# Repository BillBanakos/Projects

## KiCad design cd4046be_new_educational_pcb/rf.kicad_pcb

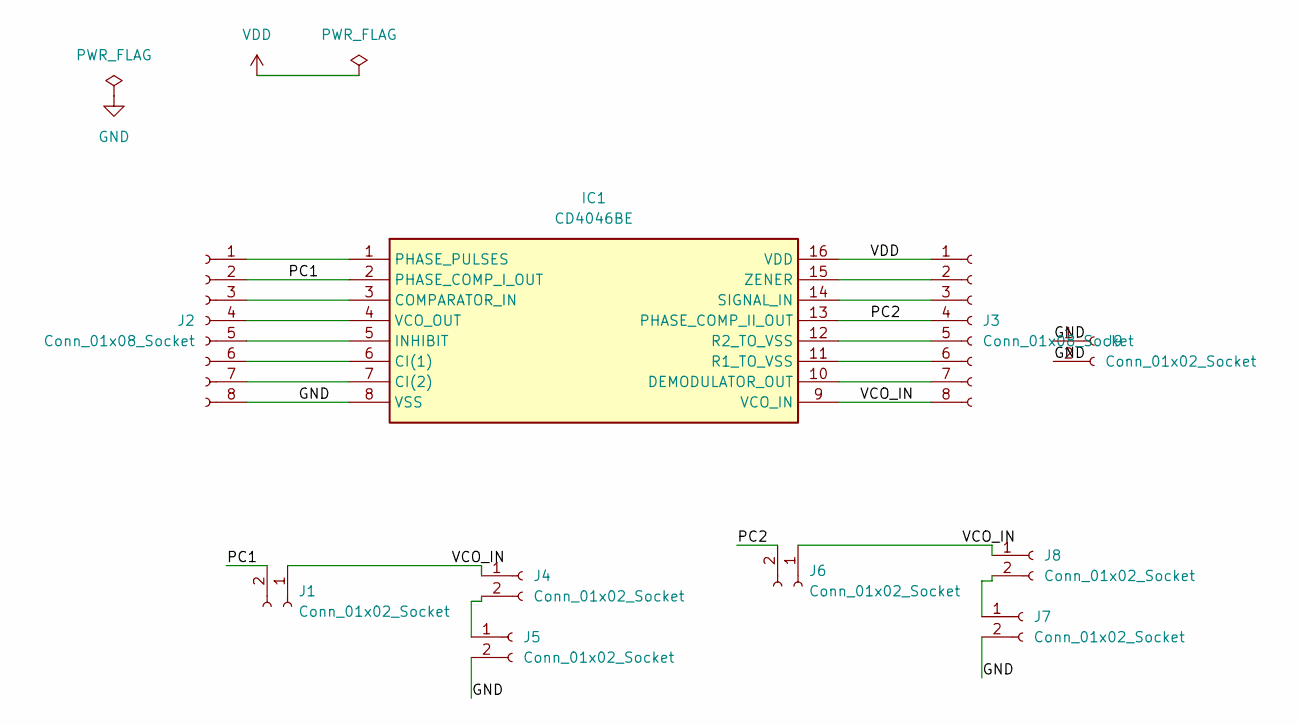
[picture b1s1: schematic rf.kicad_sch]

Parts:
IC1: CD4046BE; CERDIP-16_W7.62mm_SideBrazed; Mouser Part Number 595-CD4046BE
J1, J4, J5, J6, J7, J8, J9: Conn_01x02_Socket; PinSocket_1x02_P2.54mm_Vertical
J2, J3: Conn_01x08_Socket; PinSocket_1x08_P2.54mm_Vertical

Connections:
/PC1: IC1.2 (PHASE_COMP_I_OUT), J1.2, J2.2
/PC2: IC1.13 (PHASE_COMP_II_OUT), J3.4, J6.2
/VCO_IN: IC1.9 (VCO_IN), J1.1, J3.8, J4.1, J6.1, J8.1
GND: IC1.8 (VSS), J2.8, J5.2, J7.2, J9.1, J9.2
unnamed: IC1.6 (CI(1)), J2.6
unnamed: IC1.7 (CI(2)), J2.7
unnamed: IC1.3 (COMPARATOR_IN), J2.3
unnamed: IC1.10 (DEMODULATOR_OUT), J3.7
unnamed: IC1.5 (INHIBIT), J2.5
unnamed: IC1.1 (PHASE_PULSES), J2.1
unnamed: IC1.11 (R1_TO_VSS), J3.6
unnamed: IC1.12 (R2_TO_VSS), J3.5
unnamed: IC1.14 (SIGNAL_IN), J3.3
unnamed: IC1.4 (VCO_OUT), J2.4
unnamed: IC1.15 (ZENER), J3.2
unnamed: J4.2, J5.1
unnamed: J7.1, J8.2
VDD: IC1.16 (VDD), J3.1

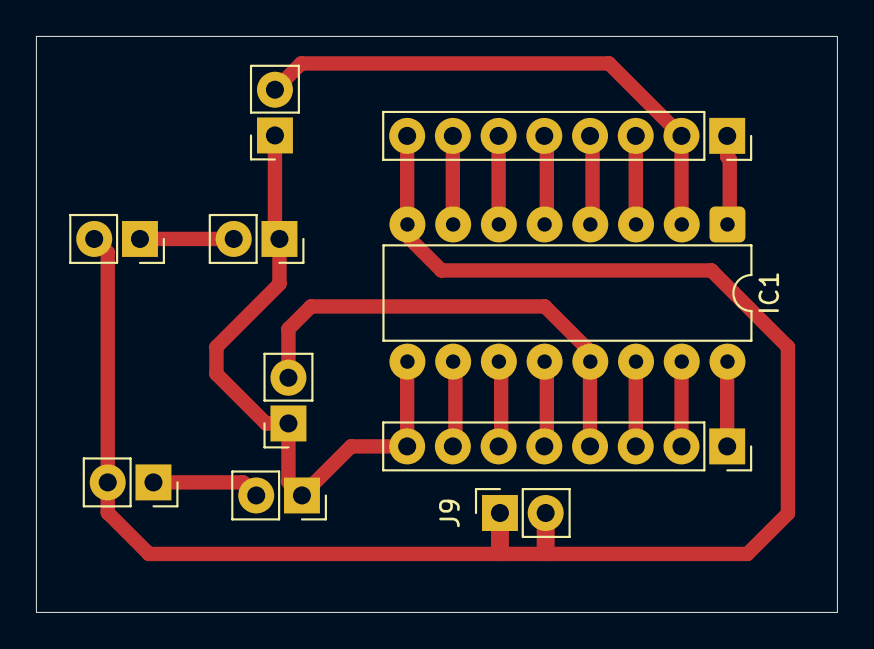
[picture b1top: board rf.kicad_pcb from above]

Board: 2 copper layers, 44.5 x 32.0 mm, 10 parts (0 on the bottom side), 18 nets.

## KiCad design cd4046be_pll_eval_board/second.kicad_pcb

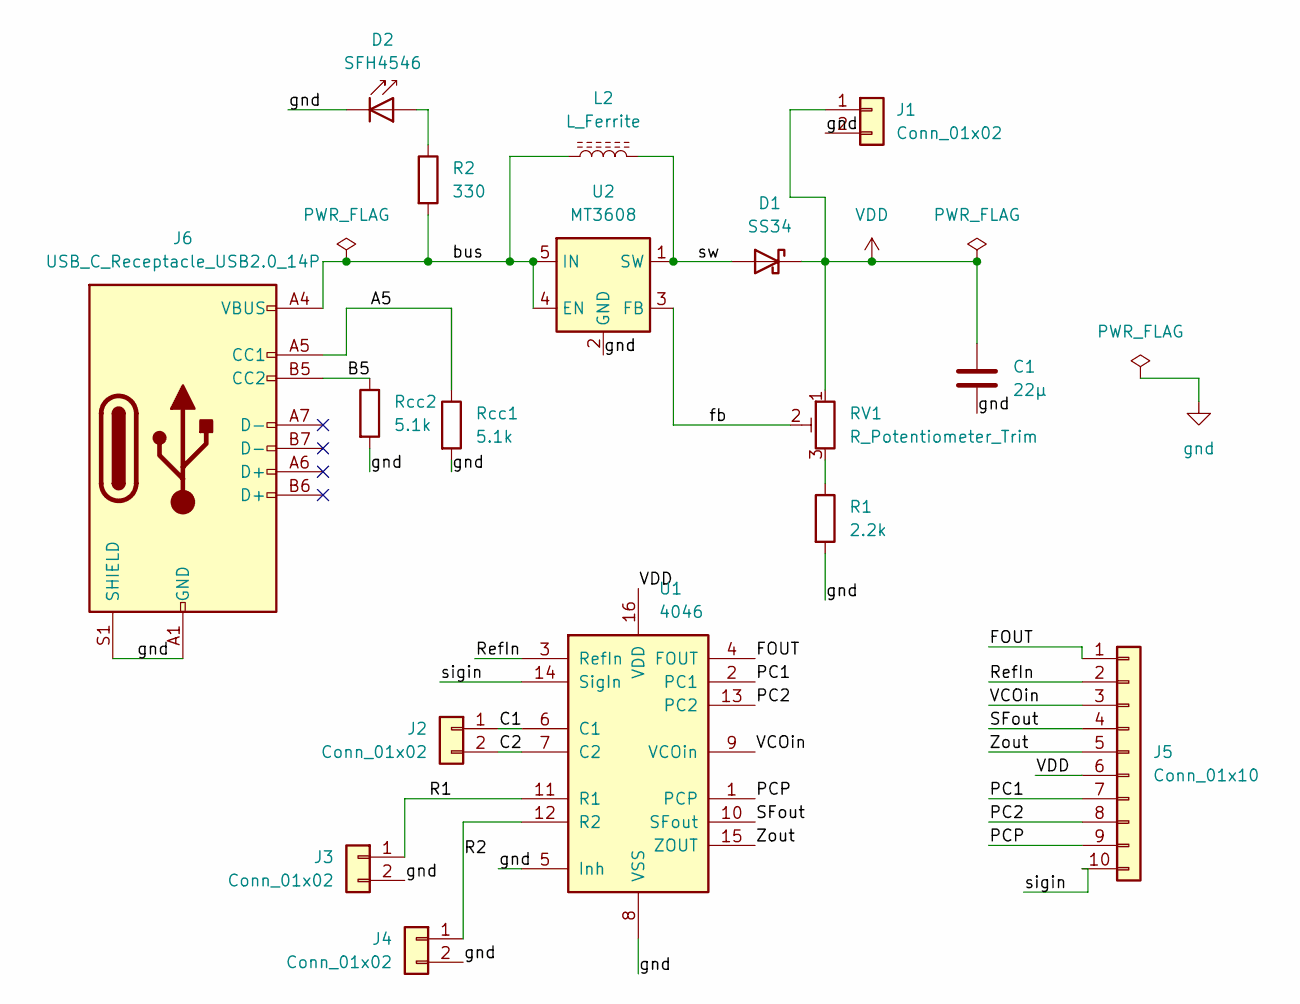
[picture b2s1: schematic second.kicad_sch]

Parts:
C1: 22μ; C_Disc_D5.0mm_W2.5mm_P5.00mm
D1: SS34; D_SMA
D2: SFH4546; LED_D5.0mm
J1: Conn_01x02; PinHeader_1x02_P2.54mm_Vertical
J2, J3, J4: Conn_01x02; PinSocket_1x02_P2.54mm_Vertical
J5: Conn_01x10; PinHeader_1x10_P2.54mm_Vertical
J6: USB_C_Receptacle_USB2.0_14P; USB_C_Receptacle_HRO_TYPE-C-31-M-12
L2: L_Ferrite; L_6.3x6.3_H3
R1: 2.2k; R_Axial_DIN0207_L6.3mm_D2.5mm_P10.16mm_Horizontal
R2: 330; R_Axial_DIN0207_L6.3mm_D2.5mm_P10.16mm_Horizontal
RV1: R_Potentiometer_Trim; Potentiometer_Bourns_3296W_Vertical
Rcc1, Rcc2: 5.1k; R_Axial_DIN0207_L6.3mm_D2.5mm_P10.16mm_Horizontal
U1: 4046; DIP-16_W7.62mm
U2: MT3608; SOT-23-6

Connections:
/A5: J6.A5 (CC1), Rcc1.1
/B5: J6.B5 (CC2), Rcc2.1
/C1: J2.1, U1.6 (C1)
/C2: J2.2, U1.7 (C2)
/FOUT: J5.1, U1.4 (FOUT)
/PC1: J5.7, U1.2 (PC1)
/PC2: J5.8, U1.13 (PC2)
/PCP: J5.9, U1.1 (PCP)
/R1: J3.1, U1.11 (R1)
/R2: J4.1, U1.12 (R2)
/RefIn: J5.2, U1.3 (RefIn)
/SFout: J5.4, U1.10 (SFout)
/VCOin: J5.3, U1.9 (VCOin)
/Zout: J5.5, U1.15 (ZOUT)
/bus: J6.A4 (VBUS), J6.A9 (VBUS), J6.B4 (VBUS), J6.B9 (VBUS), L2.1, R2.2, U2.4 (EN), U2.5 (IN)
/fb: RV1.2, U2.3 (FB)
/sigin: J5.10, U1.14 (SigIn)
/sw: D1.2 (A), L2.2, U2.1 (SW)
unnamed: D2.2 (A), R2.1
unnamed: R1.1, RV1.3
VDD: C1.1, D1.1 (K), J1.1, J5.6, RV1.1, U1.16 (VDD)
gnd: C1.2, D2.1 (K), J1.2, J3.2, J4.2, J6.A1 (GND), J6.A12 (GND), J6.B1 (GND), J6.B12 (GND), J6.S1 (SHIELD), R1.2, Rcc1.2, Rcc2.2, U1.5 (Inh), U1.8 (VSS), U2.2 (GND)

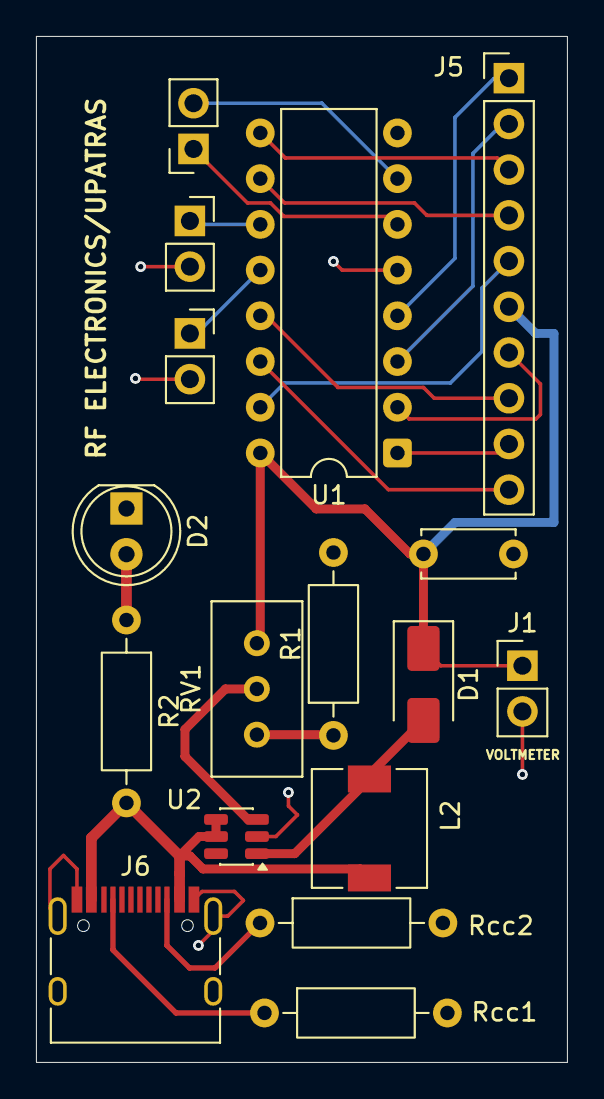
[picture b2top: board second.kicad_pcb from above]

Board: 2 copper layers, 29.5 x 57.0 mm, 17 parts (0 on the bottom side), 22 nets.

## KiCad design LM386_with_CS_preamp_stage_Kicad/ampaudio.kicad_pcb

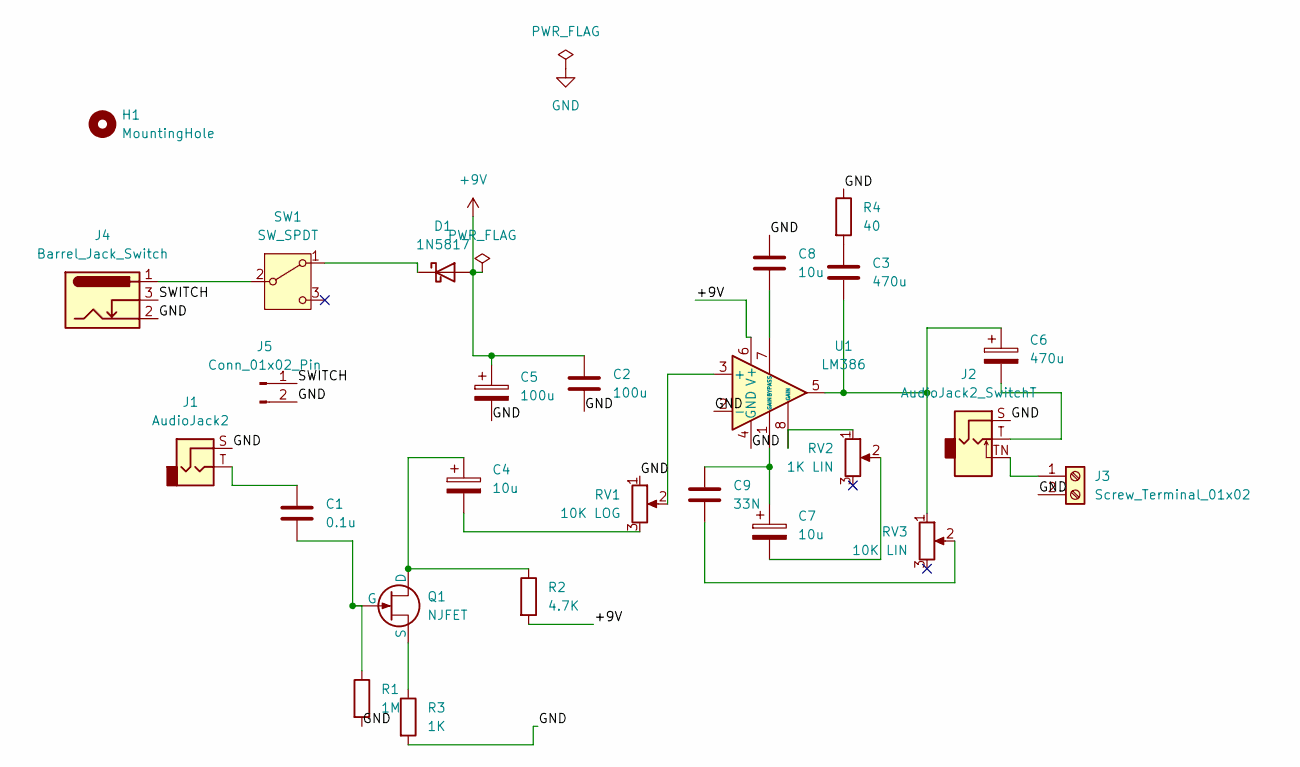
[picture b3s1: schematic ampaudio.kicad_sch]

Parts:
C1: 0.1u; C_Rect_L7.0mm_W2.5mm_P5.00mm
C2: 100u; C_Rect_L7.0mm_W2.5mm_P5.00mm
C3: 470u; C_Rect_L7.0mm_W2.5mm_P5.00mm
C4, C7: 10u; CP_Radial_D5.0mm_P2.50mm
C5: 100u; CP_Radial_D6.3mm_P2.50mm
C6: 470u; CP_Radial_D10.0mm_P5.00mm
C8: 10u; C_Rect_L7.0mm_W2.5mm_P5.00mm
C9: 33N; C_Rect_L7.0mm_W2.5mm_P5.00mm
D1: 1N5817; D_DO-41_SOD81_P10.16mm_Horizontal
H1: MountingHole; MountingHole_3.2mm_M3
J1: AudioJack2; Jack_6.35mm_Neutrik_NJ2FD-V_Vertical
J2: AudioJack2_SwitchT; Jack_6.35mm_Neutrik_NMJ4HCD2_Horizontal
J3: Screw_Terminal_01x02; TerminalBlock_Phoenix_MKDS-1,5-2-5.08_1x02_P5.08mm_Horizont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
J4: Barrel_Jack_Switch; BarrelJack_Horizontal
J5: Conn_01x02_Pin; SolderWire-0.1sqmm_1x02_P3.6mm_D0.4mm_OD1mm
Q1: NJFET; TO-92_Inline
R1: 1M; R_Axial_DIN0207_L6.3mm_D2.5mm_P10.16mm_Horizontal
R2: 4.7K; R_Axial_DIN0207_L6.3mm_D2.5mm_P10.16mm_Horizontal
R3: 1K; R_Axial_DIN0207_L6.3mm_D2.5mm_P10.16mm_Horizontal
R4: 40; R_Axial_DIN0207_L6.3mm_D2.5mm_P10.16mm_Horizontal
RV1: 10K LOG; Potentiometer_Alps_RK163_Single_Horizontal
RV2: 1K LIN; Potentiometer_Alps_RK163_Single_Horizontal
RV3: 10K LIN; Potentiometer_Alps_RK163_Single_Horizontal
SW1: SW_SPDT; SW_NKK_G1xJP
U1: LM386; DIP-8_W7.62mm

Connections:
+9V: C2.1, C5.1, D1.2 (A), R2.2, U1.6 (V+)
/SWITCH: J4.3, J5.1
GND: C2.2, C5.2, C8.1, J1.S, J2.S, J3.2, J4.2, J5.2, R1.2, R3.2, R4.1, RV1.1, U1.2 (-), U1.4 (GND)
unnamed: C1.1, J1.T
unnamed: C3.1, R4.2
unnamed: C3.2, C6.1, RV3.1, U1.5
unnamed: C4.2, RV1.3
unnamed: C6.2, J2.T
unnamed: C7.1, C9.1, U1.1 (GAIN)
unnamed: C7.2, RV2.2
unnamed: C9.2, RV3.2
unnamed: D1.1 (K), SW1.1 (A)
unnamed: J2.TN, J3.1
unnamed: C4.1, Q1.1 (D), R2.1
unnamed: C1.2, Q1.2 (G), R1.1
unnamed: Q1.3 (S), R3.1
unnamed: RV2.1, U1.8 (GAIN)
unnamed: J4.1, SW1.2 (B)
unnamed: RV1.2, U1.3 (+)
unnamed: C8.2, U1.7 (BYPASS)

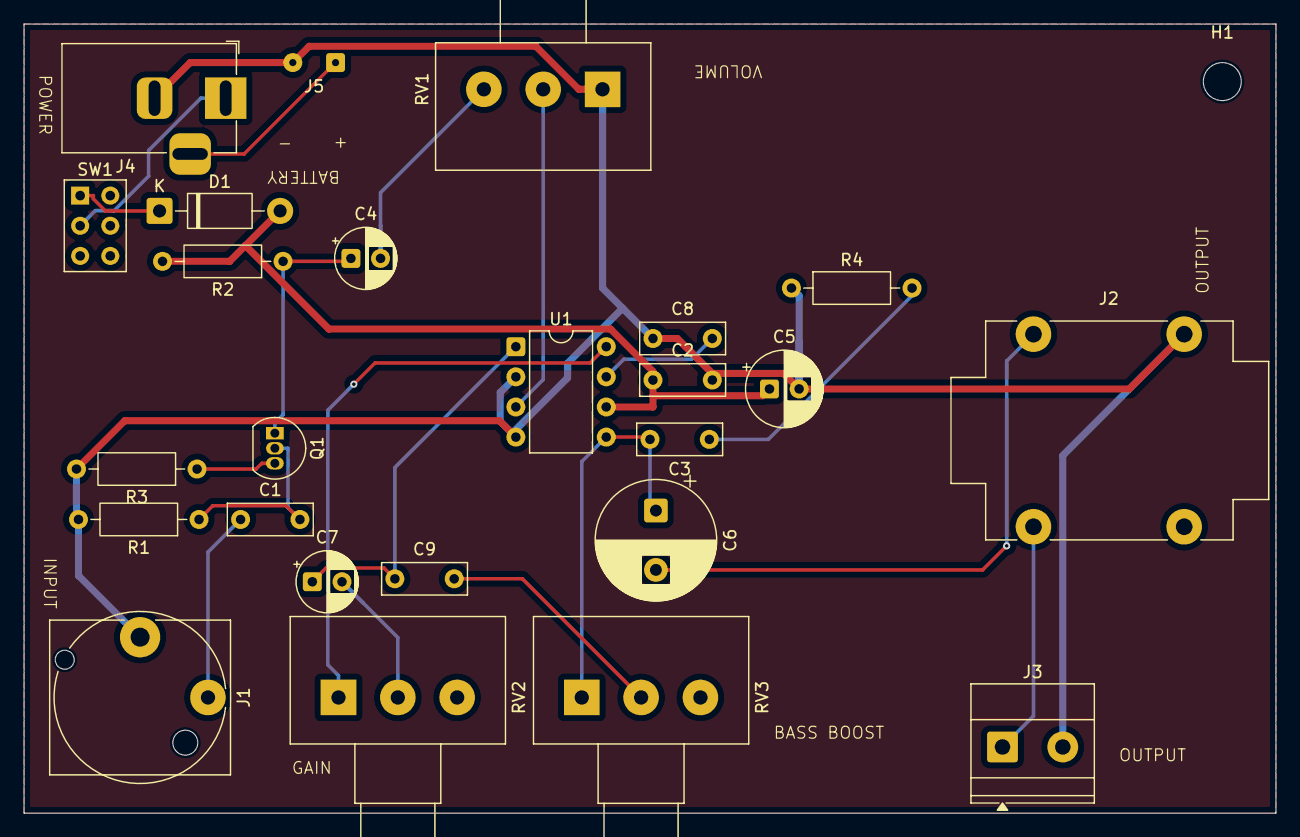
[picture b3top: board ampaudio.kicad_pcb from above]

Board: 2 copper layers, 105.5 x 66.5 mm, 26 parts (0 on the bottom side), 20 nets.

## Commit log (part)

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2026-02-28 videos_new
2026-03-05 colpitts
2026-03-05 rename
2026-06-02 koul
2026-06-14 antenna
